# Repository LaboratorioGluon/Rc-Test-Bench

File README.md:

# Rc-Test-Bench

Projecto para caracterización de motores RC.

## Componentes:

- STM32 [Link](https://s.click.aliexpress.com/e/_Dma6yBh)
- Célula de Carga (El peso que miden depende del motor que quieras probar) [Link](https://s.click.aliexpress.com/e/_DmU0uxv)
- Hx711 [Link](https://s.click.aliexpress.com/e/_Dd5aIMT)
- Modulo: sensor de corriente INA219 [Link](https://s.click.aliexpress.com/e/_Dmx4wbh)
- ACS712-20A [Link](https://s.click.aliexpress.com/e/_DkJqOTh)

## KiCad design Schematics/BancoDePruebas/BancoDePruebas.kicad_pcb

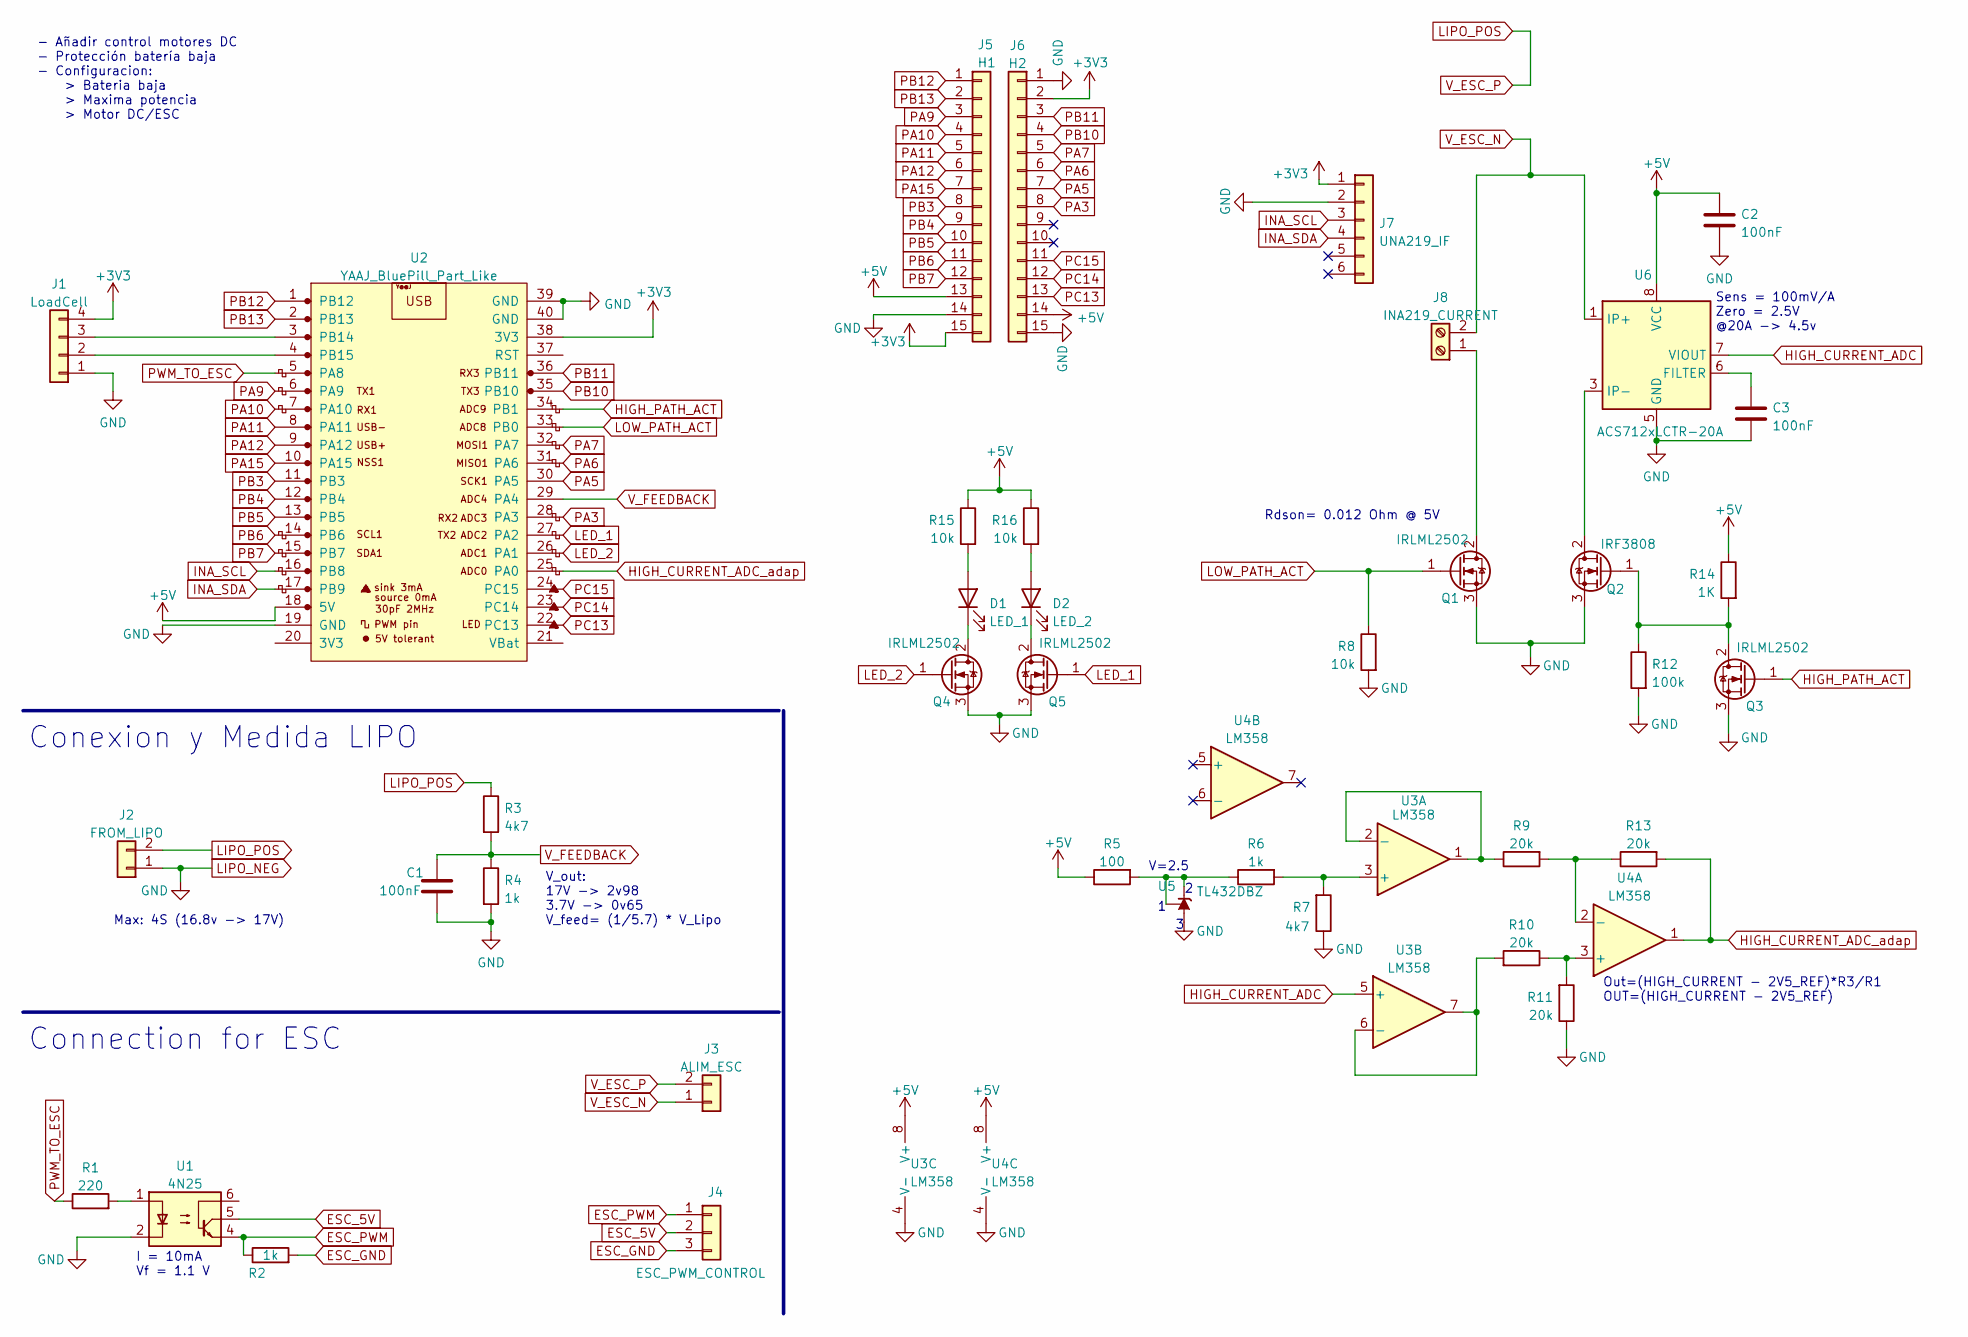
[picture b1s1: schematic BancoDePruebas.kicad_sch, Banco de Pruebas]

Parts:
C1, C2, C3: 100nF; C_1206_3216Metric_Pad1.33x1.80mm_HandSolder
D1: LED_1; LED_D5.0mm
D2: LED_2; LED_D5.0mm
J1: LoadCell; PinHeader_1x04_P2.54mm_Vertical
J2: FROM_LIPO; AMASS_XT30U-F_1x02_P5.0mm_Vertical
J3: ALIM_ESC; AMASS_XT30U-F_1x02_P5.0mm_Vertical
J4: ESC_PWM_CONTROL; PinHeader_1x03_P2.54mm_Vertical
J5: H1; PinHeader_1x15_P2.54mm_Vertical
J6: H2; PinHeader_1x15_P2.54mm_Vertical
J7: UNA219_IF; PinHeader_1x06_P2.54mm_Vertical
J8: INA219_CURRENT; TerminalBlock_bornier-2_P5.08mm
Q1, Q3, Q4, Q5: IRLML2502; SOT-23_Handsoldering
Q2: IRF3808; TO-220-3_Vertical
R1: 220; R_1206_3216Metric_Pad1.30x1.75mm_HandSolder
R2, R4, R6: 1k; R_1206_3216Metric_Pad1.30x1.75mm_HandSolder
R3, R7: 4k7; R_1206_3216Metric_Pad1.30x1.75mm_HandSolder
R5: 100; R_1206_3216Metric_Pad1.30x1.75mm_HandSolder
R8, R15, R16: 10k; R_1206_3216Metric_Pad1.30x1.75mm_HandSolder
R9, R10, R11, R13: 20k; R_1206_3216Metric_Pad1.30x1.75mm_HandSolder
R12: 100k; R_1206_3216Metric_Pad1.30x1.75mm_HandSolder
R14: 1K; R_1206_3216Metric_Pad1.30x1.75mm_HandSolder
U1: 4N25; DIP-6_W7.62mm
U2: YAAJ_BluePill_Part_Like; YAAJ_BluePill_1b
U3, U4: LM358; SOP-8_3.9x4.9mm_P1.27mm
U5: TL432DBZ; SOT-23
U6: ACS712xLCTR-20A; SOIC-8_3.9x4.9mm_P1.27mm

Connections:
+3V3: J1.4, J5.15, J6.2, J7.1, U2.38 (3V3)
+5V: C2.1, J5.13, J6.14, R5.1, R14.1, R15.1, R16.1, U2.18 (5V), U3.8 (V+), U4.8 (V+), U6.8 (VCC)
ESC_5V: J4.2, U1.5
ESC_GND: J4.3, R2.2
ESC_PWM: J4.1, R2.1, U1.4
HIGH_CURRENT_ADC: U3.5 (+), U6.7 (VIOUT)
HIGH_CURRENT_ADC_adap: R13.2, U2.25 (PA0), U4.1
HIGH_PATH_ACT: Q3.1 (G), U2.34 (PB1)
INA_SCL: J7.3, U2.16 (PB8)
INA_SDA: J7.4, U2.17 (PB9)
LED_1: Q5.1 (G), U2.27 (PA2)
LED_2: Q4.1 (G), U2.26 (PA1)
LIPO_NEG: C1.2, C2.2, C3.2, J1.1, J2.1, J5.14, J6.1, J6.15, J7.2, Q1.3 (S), Q2.3 (S), Q3.3 (S), Q4.3 (S), Q5.3 (S), R4.2, R7.1, R8.2, R11.1, R12.2, U1.2, U2.19 (GND), U2.39 (GND), U2.40 (GND), U3.4 (V-), U4.4 (V-), U5.3 (A), U6.5 (GND)
LIPO_POS: J2.2, J3.2, R3.1
LOW_PATH_ACT: Q1.1 (G), R8.1, U2.33 (PB0)
unnamed: D1.1 (K), Q4.2 (D)
unnamed: D1.2 (A), R15.2
unnamed: D2.1 (K), Q5.2 (D)
unnamed: D2.2 (A), R16.2
unnamed: J1.2, U2.4 (PB15)
unnamed: J1.3, U2.3 (PB14)
unnamed: J8.1, Q1.2 (D)
unnamed: Q2.1 (G), Q3.2 (D), R12.1, R14.2
unnamed: Q2.2 (D), U6.3 (IP-), U6.4 (IP-)
unnamed: R1.2, U1.1
unnamed: R5.2, R6.1, U5.1 (REF), U5.2 (K)
unnamed: R6.2, R7.2, U3.3 (+)
unnamed: R9.1, U3.1, U3.2 (-)
unnamed: R10.1, R11.2, U4.3 (+)
unnamed: R10.2, U3.6 (-), U3.7
unnamed: R9.2, R13.1, U4.2 (-)
unnamed: C3.1, U6.6 (FILTER)
PA3: J6.8, U2.28 (PA3)
PA5: J6.7, U2.30 (PA5)
PA6: J6.6, U2.31 (PA6)
PA7: J6.5, U2.32 (PA7)
PA9: J5.3, U2.6 (PA9)
PA10: J5.4, U2.7 (PA10)
PA11: J5.5, U2.8 (PA11)
PA12: J5.6, U2.9 (PA12)
PA15: J5.7, U2.10 (PA15)
PB3: J5.8, U2.11 (PB3)
PB4: J5.9, U2.12 (PB4)
PB5: J5.10, U2.13 (PB5)
PB6: J5.11, U2.14 (PB6)
PB7: J5.12, U2.15 (PB7)
PB10: J6.4, U2.35 (PB10)
PB11: J6.3, U2.36 (PB11)
PB12: J5.1, U2.1 (PB12)
PB13: J5.2, U2.2 (PB13)
PC13: J6.13, U2.22 (PC13)
PC14: J6.12, U2.23 (PC14)
PC15: J6.11, U2.24 (PC15)
PWM_TO_ESC: R1.1, U2.5 (PA8)
V_ESC_N: J3.1, J8.2, U6.1 (IP+), U6.2 (IP+)
V_FEEDBACK: C1.1, R3.2, R4.1, U2.29 (PA4)

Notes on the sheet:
- Añadir control motores DC - Protección batería baja - Configuracion: > Bateria baja > Maxima potencia > Motor DC/ESC
Out=(HIGH_CURRENT - 2V5_REF)*R3/R1 OUT=(HIGH_CURRENT - 2V5_REF)
Connection for ESC
V_out: 17V -> 2v98 3.7V -> 0v65 V_feed= (1/5.7) * V_Lipo
Max: 4S (16.8v -> 17V)
Rdson= 0.012 Ohm @ 5V
I = 10mA Vf = 1.1 V
V=2.5
Sens = 100mV/A Zero = 2.5V @20A -> 4.5v
Conexion y Medida LIPO

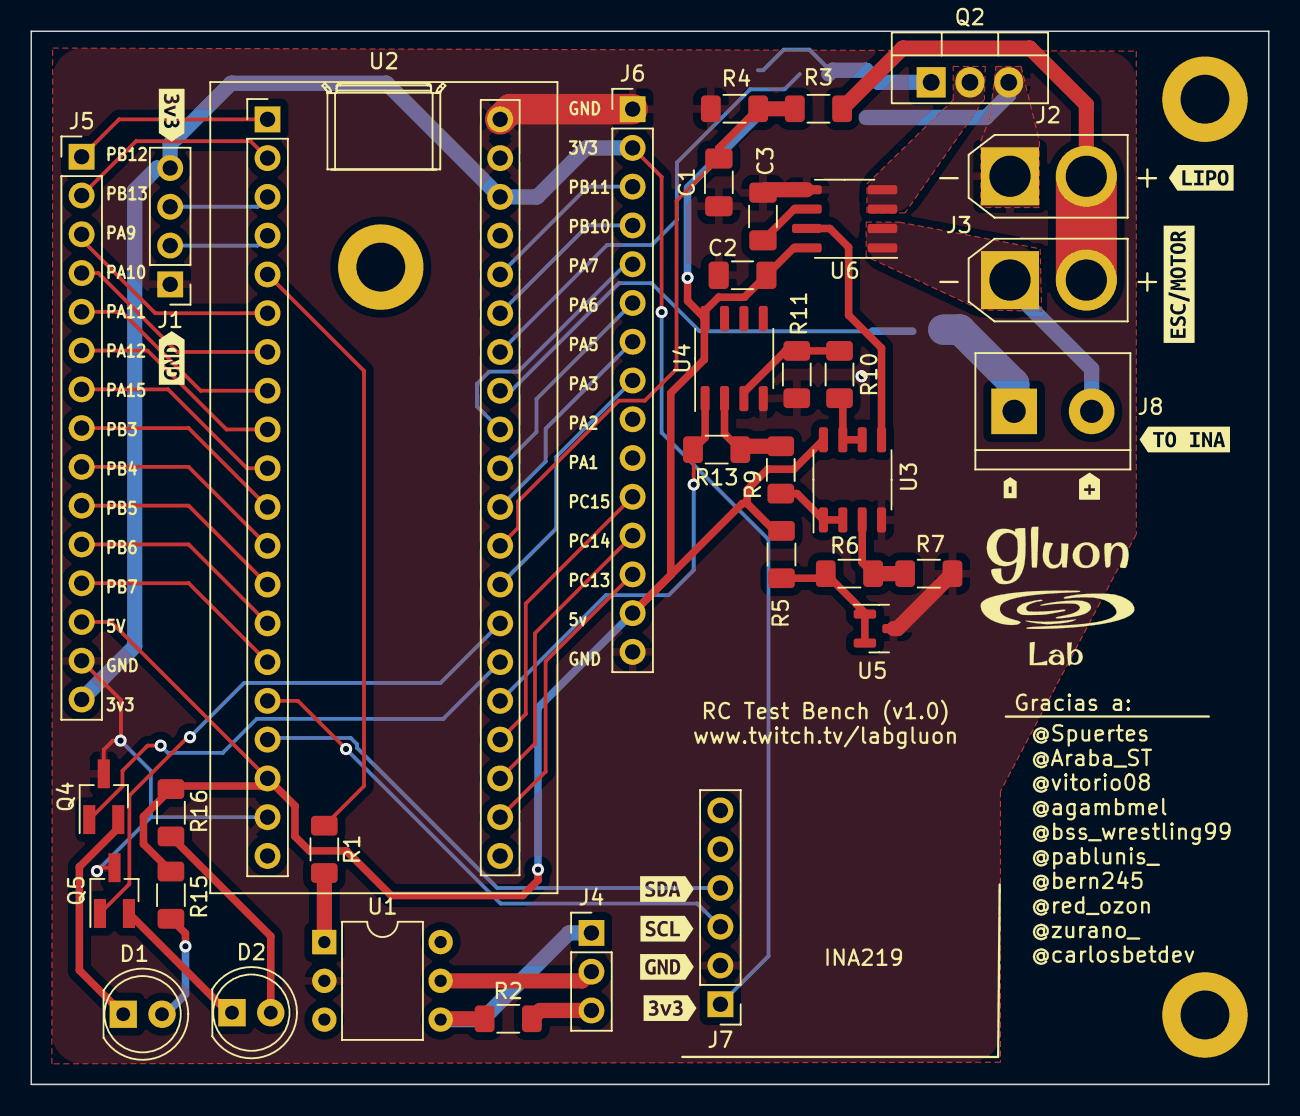
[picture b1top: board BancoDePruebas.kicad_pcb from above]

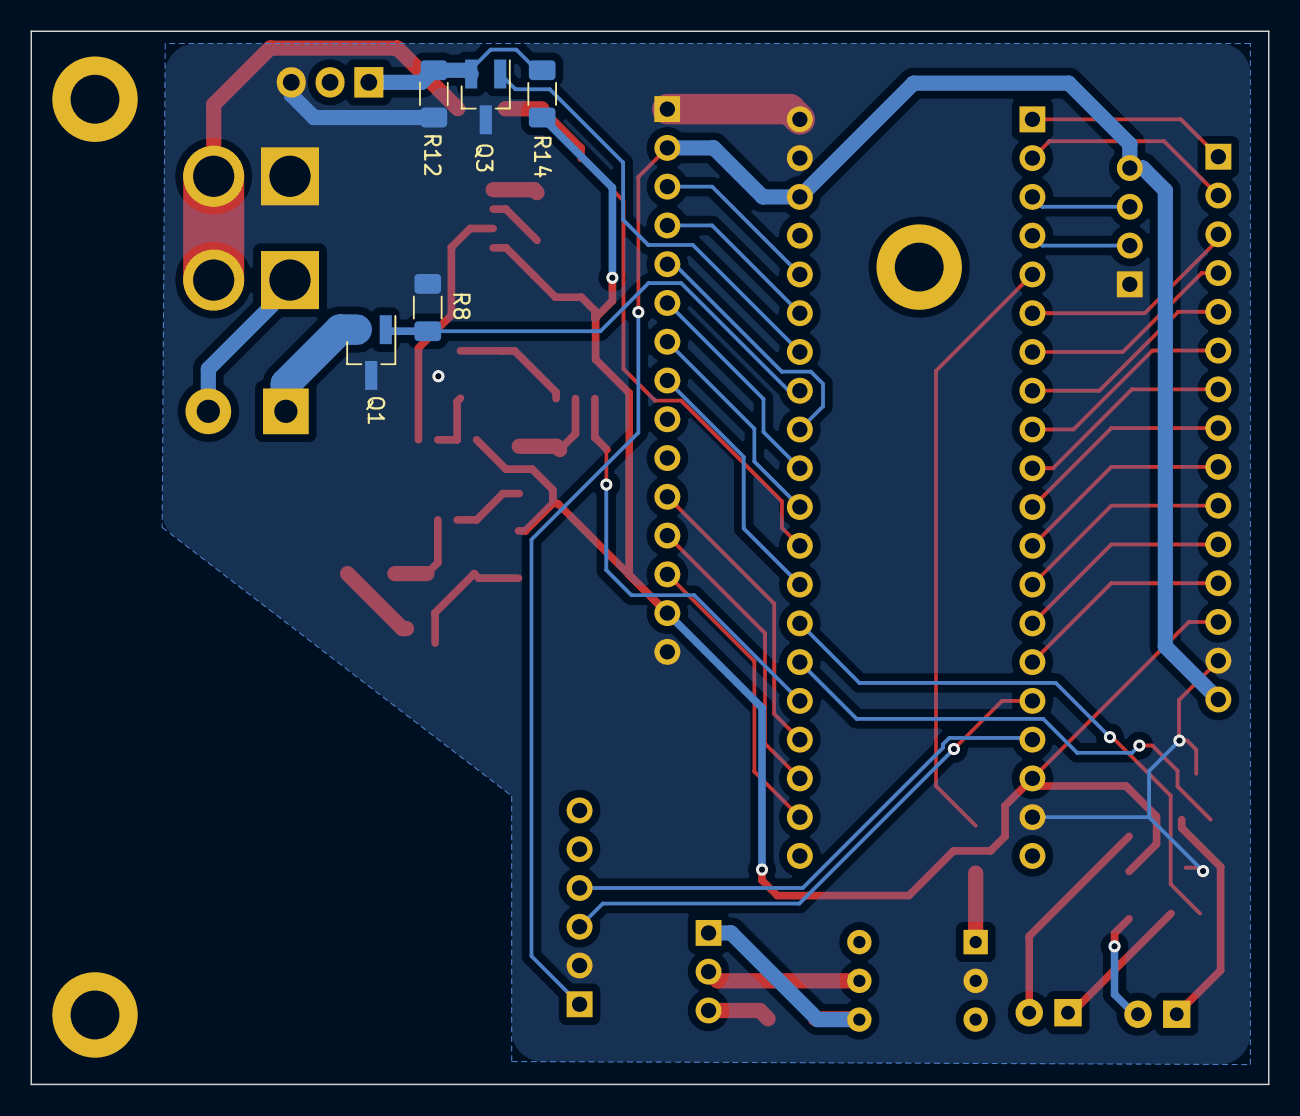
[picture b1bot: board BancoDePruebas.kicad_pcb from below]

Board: 2 copper layers, 81.1 x 69.0 mm, 51 parts (5 on the bottom side), 56 nets.

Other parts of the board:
kibuzzard-635D7BB9: G***; kibuzzard-635D7BB9
kibuzzard-635D7BC7: G***; kibuzzard-635D7BC7
kibuzzard-6356CD5A, kibuzzard-6356CD5A#2: G***; kibuzzard-6356CD5A
kibuzzard-6356CD7C: G***; kibuzzard-6356CD7C
kibuzzard-6356CD66, kibuzzard-6356CD66#2: G***; kibuzzard-6356CD66
kibuzzard-6356CD87: G***; kibuzzard-6356CD87
kibuzzard-6356CE02: G***; kibuzzard-6356CE02
kibuzzard-6356CE38: G***; kibuzzard-6356CE38
kibuzzard-6356CE47: G***; kibuzzard-6356CE47

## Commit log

2022-10-31 Version pre-release
2022-10-31 Fixes for DRC
2022-11-01 Imagen nueva
2022-11-05 Deleted malformed submodule
2022-11-05 Added Source code
2022-11-06 Working ping back
2022-11-07 Added PING check and EMERGENCY stop
2022-11-19 Added battery limit and config page
2022-11-19 Changes in UI
